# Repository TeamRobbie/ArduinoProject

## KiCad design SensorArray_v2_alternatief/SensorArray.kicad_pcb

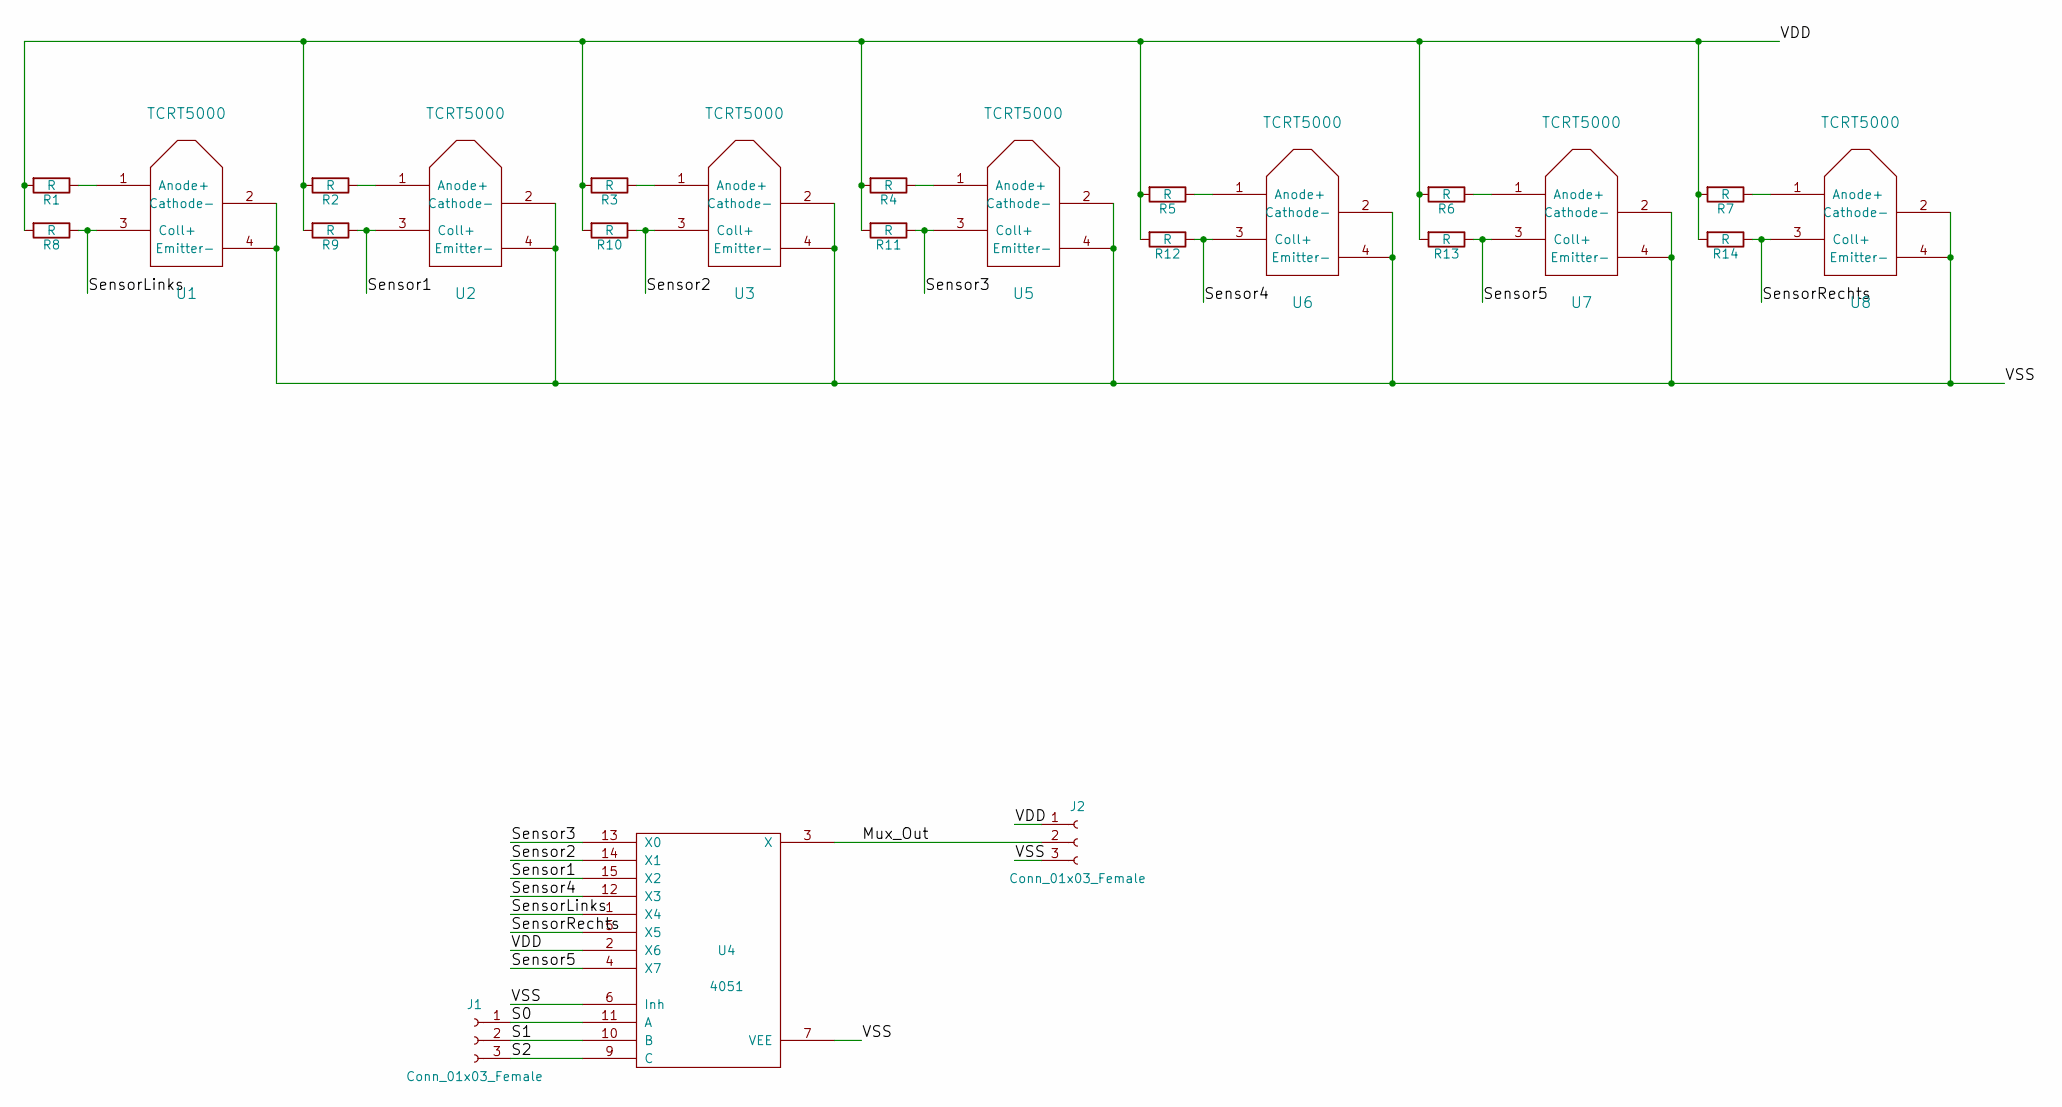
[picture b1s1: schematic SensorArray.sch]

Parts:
J1, J2: Conn_01x03_Female; Pin_Header_Straight_1x03_Pitch2.54mm
R1, R2, R3, R4, R5, R6, R7, R8, R9, R10, R11, R12, R13, R14: R; R_Axial_DIN0204_L3.6mm_D1.6mm_P7.62mm_Horizontal
U1, U2, U3, U5, U6, U7, U8: TCRT5000
U4: 4051; DIP-16_W7.62mm_LongPads

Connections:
/Mux_Out: J2.2, U4.3 (X)
/S0: J1.1, U4.11 (A)
/S1: J1.2, U4.10 (B)
/S2: J1.3, U4.9 (C)
/Sensor1: R9.1, U2.3 (Coll+), U4.15 (X2)
/Sensor2: R10.1, U3.3 (Coll+), U4.14 (X1)
/Sensor3: R11.1, U4.13 (X0), U5.3 (Coll+)
/Sensor4: R12.1, U4.12 (X3), U6.3 (Coll+)
/Sensor5: R13.1, U4.4 (X7), U7.3 (Coll+)
/SensorLinks: R8.1, U1.3 (Coll+), U4.1 (X4)
/SensorRechts: R14.1, U4.5 (X5), U8.3 (Coll+)
unnamed: R1.1, U1.1 (Anode+)
unnamed: R2.1, U2.1 (Anode+)
unnamed: R3.1, U3.1 (Anode+)
unnamed: R4.1, U5.1 (Anode+)
unnamed: R5.1, U6.1 (Anode+)
unnamed: R6.1, U7.1 (Anode+)
unnamed: R7.1, U8.1 (Anode+)
VDD: J2.1, R1.2, R2.2, R3.2, R4.2, R5.2, R6.2, R7.2, R8.2, R9.2, R10.2, R11.2, R12.2, R13.2, R14.2, U4.2 (X6), U4.16 (VDD)
VSS: J2.3, U1.2 (Cathode-), U1.4 (Emitter-), U2.2 (Cathode-), U2.4 (Emitter-), U3.2 (Cathode-), U3.4 (Emitter-), U4.6 (Inh), U4.7 (VEE), U4.8 (VSS), U5.2 (Cathode-), U5.4 (Emitter-), U6.2 (Cathode-), U6.4 (Emitter-), U7.2 (Cathode-), U7.4 (Emitter-), U8.2 (Cathode-), U8.4 (Emitter-)

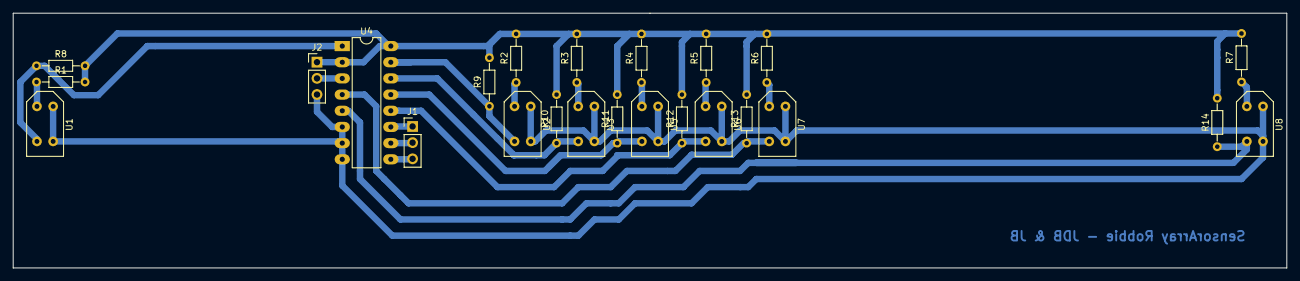
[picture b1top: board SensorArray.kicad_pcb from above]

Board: 2 copper layers, 200.0 x 40.0 mm, 24 parts (0 on the bottom side), 20 nets.

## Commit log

2017-11-07 readme toegevoegd
2017-11-07 drive.h en drive.cpp toegevoegd
    deze moeten functies bevatten om L R F B te rijden
2017-11-07 Drive.ino toegevoegd
    voorlopige versie, verhouding van draaisnelheid tussen de twee wielen moeten nog getweaked worden
2017-11-07 Drive.ino aangepast met een factor voor bochten te nemen
    We kunnen nu een factor tussen 0.8 en 1 toevoegen voor het draaien en vooruit/achteruit rijden.
2017-11-07 Rechter wiel laten vertragen om naar rechts te rijden voor optimale snelheid. Remmen kan toegepast worden door de wielen te vertragen.
2017-11-07 Dempende factor toegevoegd ipv aansturende aan alle rijrichtingen
2017-11-07 bochten afgewerkt
2017-11-08 kicad ontwerp toegevoegd
2017-11-08 verder gewerkt aan motor shield
2017-11-08 verder aanpassingen om perfect rechtdoor te rijden + void donut() toegevoegd
2017-11-09 4 voids in 1 void met switch case gestoken
2017-11-09 drive met library gemaakt en .ino aangepast
2017-11-09 driveScale toegevoegd
    Methode driveScale toegevoegd waarmee het wagentje vooruit kan rijden met een bocht aan de hand van deze schaalfactor van -100 (links) tot 100 (rechts) met 0=rechtdoor
2017-11-14 schets van Robbie toegevoegd
2017-11-14 schema van line track / IR - sensor toegevoegd
2018-02-25 Toevoeging SensorArray PCB, testcode, batterijhouder en diverse
    KiCad PCB-ontwerp van SensorArray toegevoegd
    Arduino-testing code toegevoegd
    Prototype van library voor sensoren uit te lezen toegevoegd (te testen)
    SolidWorks-ontwerp voor prototype batterijhouder toegevoegd
    Minor changes aan bestaande Drive-code en libraries
2018-03-21 Toevoeging Arduino-code, libraries, ...
    Grote update met alle testcode voor Arduino met libraries: Drive, Hallsensoren, IRSensoren
2018-03-30 Libraries en arduino-programma bijgewerkt
    Aanpassingen aan libraries voor met zijsensoren in te lezen
    Toevoeging van snelheidsmeter-functionaliteit met hallsensoren
2018-04-11 Grote update
    Update met toevoeging van Bluetooth- en RFID-lezer-functionaliteit, geupdate libraries en toevoeging libraries voor RFID, documentatie omtrent pintoewijzing,...
2018-04-11 Arduino-RPi interactie toegevoegd
    Functionaliteit om snelheid en PID-waardes mee te geven vanaf Raspberry Pi toegevoegd.
2018-04-13 Wijzigingen in Bluetooth-communicatie en PID-regeling
    Bluetooth-communicatie met RPi verbeterd
    PID-regeling aangepast
2018-04-18 Kleine wijziging in libraries, Excel bestand met inlezen toegevoegd
    Correctie in snelheidsbepaling van HallSensoren-library
    Aanpassing IRSensoren-library voor over Bluetooth te printen
    Toevoeging Excel bestand met uitleg over IR-Sensoren
